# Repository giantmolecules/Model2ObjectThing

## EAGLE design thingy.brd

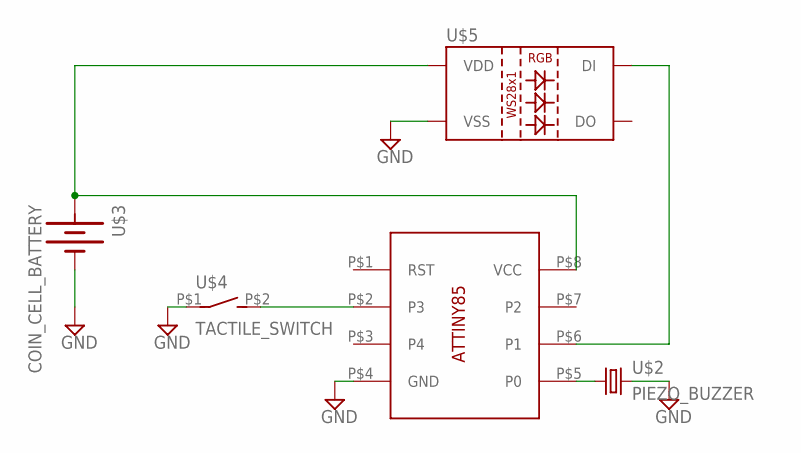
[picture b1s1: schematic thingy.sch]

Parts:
U$1: ATTINY85-SOCKET; DIP8SOCKET
U$2: PIEZO_BUZZER
U$3: COIN_CELL_BATTERY; COIN_BATTERY
U$4: TACTILE_SWITCH
U$5: 5MM-NEOPIXEL; T1-3/4-LED

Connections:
GND: U$1.P$4 (GND), U$2.P$2 (2), U$3.P$2 (-), U$4.P$1, U$5.P$3 (VSS)
unnamed: U$1.P$8 (VCC), U$3.P$1 (+), U$5.P$2 (VDD)
unnamed: U$1.P$2 (P3), U$4.P$2 (S)
unnamed: U$1.P$5 (P0), U$2.P$1 (1)
unnamed: U$1.P$6 (P1), U$5.P$1 (DI)

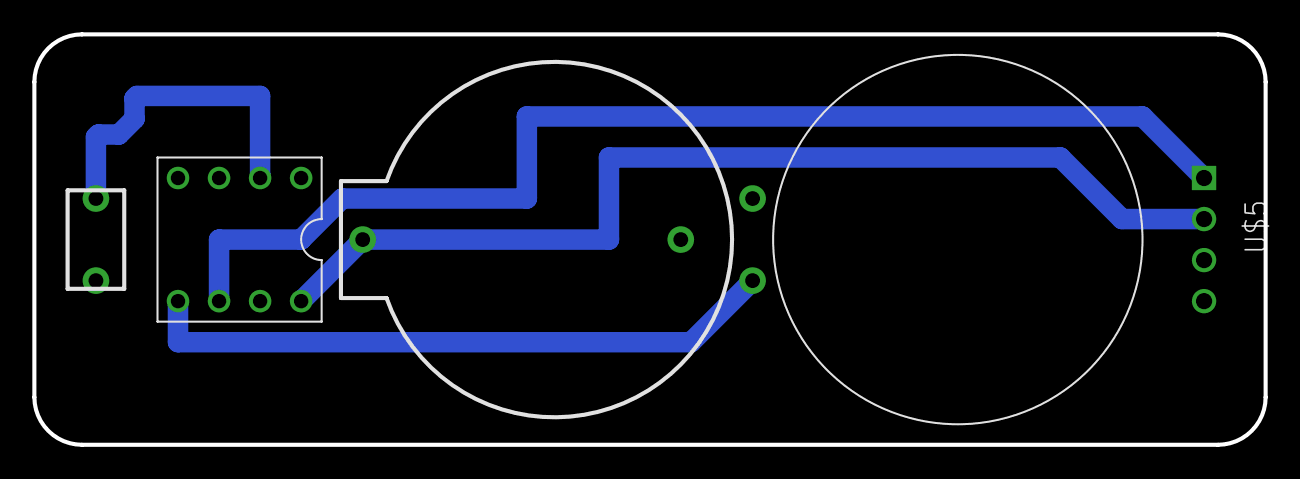
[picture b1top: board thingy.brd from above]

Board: 2 copper layers, 76.2 x 25.4 mm, 5 parts (0 on the bottom side), 5 nets.

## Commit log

2019-10-08 init
